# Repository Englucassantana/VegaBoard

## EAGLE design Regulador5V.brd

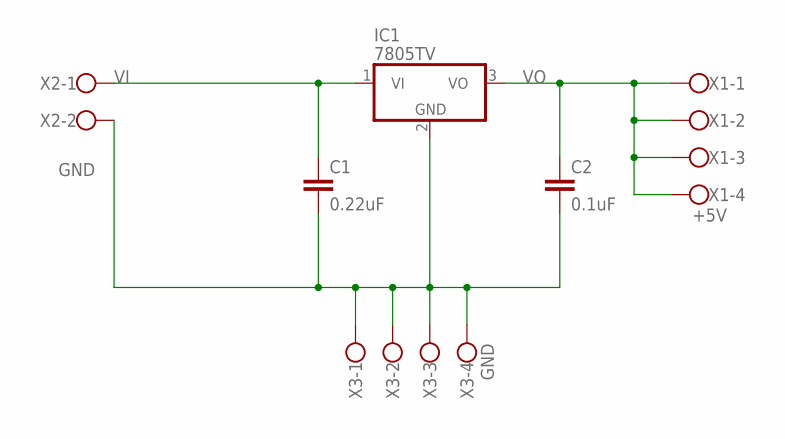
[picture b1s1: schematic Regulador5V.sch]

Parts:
C1: 0.22uF; C2.5-2
C2: 0.1uF; C2.5-2
IC1: 7805TV; TO220V
X1: +5V; W237-4
X2: W237-102
X3: GND; W237-4

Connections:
GND: C1.2, C2.2, IC1.2 (GND), X2.2, X3.1, X3.2, X3.3, X3.4
VI: C1.1, IC1.1 (VI), X2.1
VO: C2.1, IC1.3 (VO), X1.1, X1.2, X1.3, X1.4

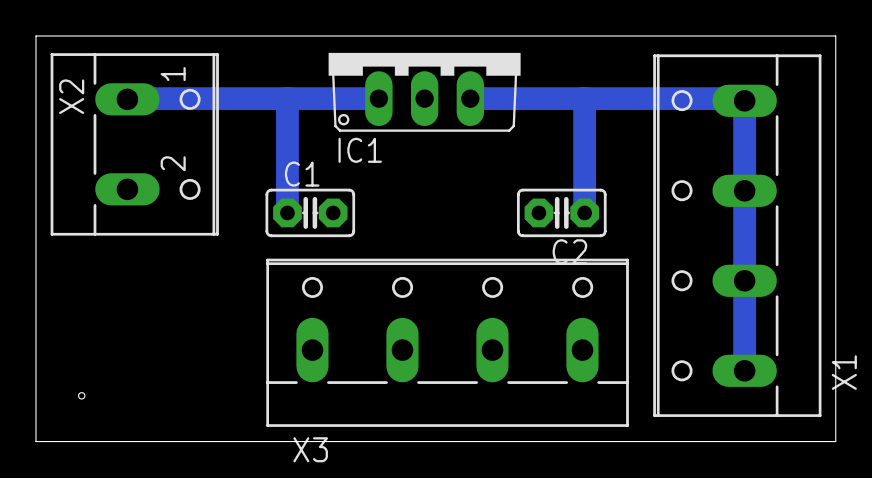
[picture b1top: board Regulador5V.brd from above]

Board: 2 copper layers, 44.4 x 22.5 mm, 6 parts (0 on the bottom side), 3 nets.
